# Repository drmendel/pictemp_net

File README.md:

<div align="center">
  
</div>

## Overview

The **`PICTEMP.NET`** is a standalone IoT temperature sensor based on the *PIC18F97J60*, featuring TCP access over Ethernet using the *ENC28J60* ethernet controller. Includes custom firmware built on the Microchip TCP/IP stack and a compact KiCad-designed PC (similar to *PICDEM2.NET*) ideal for IoT, home automation, and industrial monitoring.

The project demonstrates a full-stack IoT solution:

- **Hardware**: A compact, efficient PCB designed in *KiCad*
- **Firmware**: Integrating sensor acquisition and network communication based on *Microchip Solutions v2011-06-02 TCP/IP Demo App*

The project was tested on the *PICDEM2.NET* development board, which ensured the firmware functionality before transitioning to the custom PCB.

## Hardware

### Core Components

- **Microcontroller:** PIC18F97J60  
- **Ethernet Controller:** ENC28J60 (external)  
- **Temperature Sensor:** TC1047x47  
- **Clock Sources:** 25 MHz, 32 kHz crystals  
- **Power Regulation:** LM2940S-5.0, TC1262-3.3  
- **LCD Display:** LCM-S01602DTR_M  
- **Connectivity:** RJ-12, RJ-45, barrel jack, pushbutton, testpoints

*The full list is available in [*pictempnet.csv*](hardware/pictempnet.csv).*

### Design priorities

- Compact footprint for embedded deployment  
- Efficient routing for signals and power  
- Smaller size to reduce cost and complexity    

### PCB Layout

|  |  |  |
|-|-|-|
| *Top view* | *Right view* | *Left view* |

*More images are available in the [images/](hardware/images) folder.*

## Firmware Architecture

The firmware is based on *Microchip Solutions v2011-06-02 TCP/IP Demo App*, modified to implement temperature sensing functionality. Key components include:  

- *`temperature_sensor.h` / `temperature_sensor.c`* – Interfaces directly with the temperature sensor IC, reading real-time measurements and providing functions to access the data.    
- *`GenericTCPIPServer.c`* – Derived from Microchip sources, enhanced for temperature sensor integration and real-time TCP access.

The firmware manages:  

- TCP connection handling and client requests  
- Temperature sensor sampling on TCP request
- Data buffering and formatting
- Efficient, low-latency response for real-time monitoring  

## Usage

### Project Configuration

The firmware is developed using *Microchip MPLAB X IDE*. It is strongly recommended to compile the project with this IDE due to complex configuration requirements.

In the project properties, set the following options:

- **Categories:** `C18-PICDN2_ENC28`  
- **Device:** `PIC18F97J60`  
- **Compiler Toolchain:** *[`C18 v3.47`](https://mplab-c18.software.informer.com/download/)*  

### Steps to Use

1. **Flash** the firmware to the custom *PCB* or the *PICDEM2.NET* development board.  
2. **Connect** the device to your network via Ethernet. The LCD will display the assigned IP address.  
3. **Access** temperature readings by sending the character `'t'` or `'T'` to *TCP port 2000*.

## Licensing

- **Hardware design**: Licensed under the [CERN-OHL-W-2.0](./hardware/LICENSE).  
- **Firmware**: Licensed under the terms of the [MICROCHIP SOFTWARE LICENSE AGREEMENT](./firmware/LICENSE).  

By **`DOWNLOADING`** or **`USING`** any part of this repository (including but not limited to source code, hardware design files, schematics, documentation, and images) through methods such as:
  - cloning the repository (`git clone ...`)  
  - downloading release archives (`.zip` / `.tar.gz`)  
  - forking the repository  
  - downloading individual files via the GitHub web interface  
  - retrieving the repository via GitHub API or GitHub CLI  
  - mirroring the repository

you **`AGREE`** to the applicable license terms, including the [MICROCHIP SOFTWARE LICENSE AGREEMENT](./firmware/LICENSE).

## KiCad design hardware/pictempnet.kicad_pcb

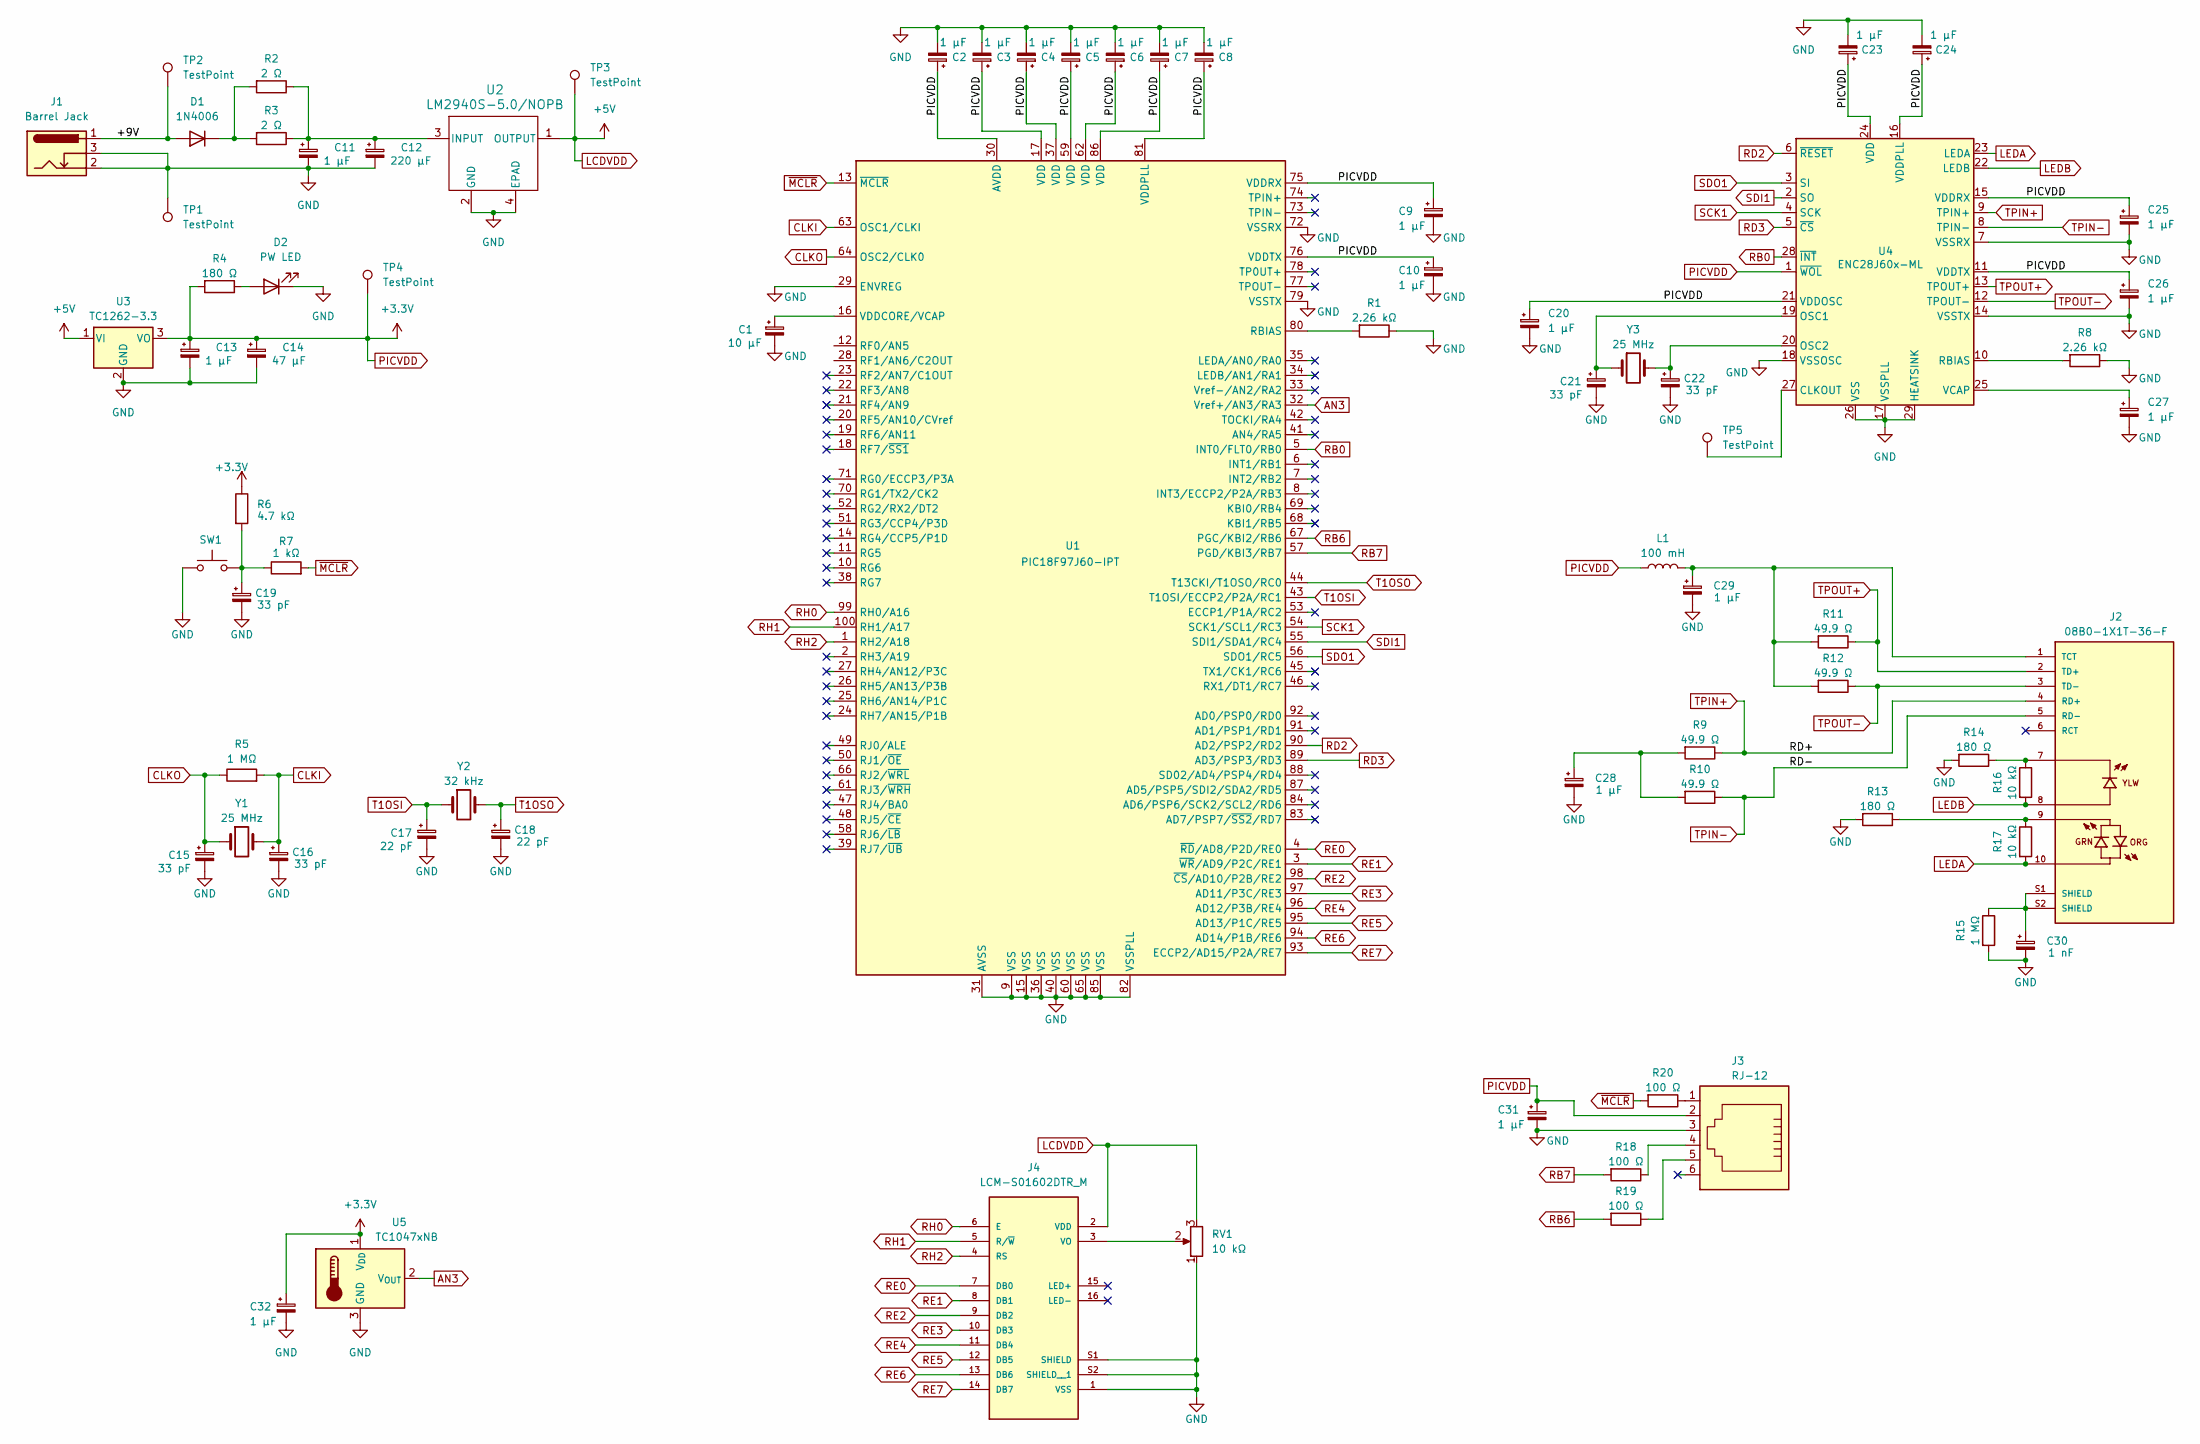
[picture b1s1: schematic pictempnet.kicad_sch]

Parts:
C1: 10 μF; CP_EIA-1608-08_AVX-J_Pad1.25x1.05mm_HandSolder
C2, C3, C4, C5, C6, C7, C8, C9, C10, C11, C13, C20, C23, C24, C25, C26, C27, C28, C29, C31, C32: 1 μF; CP_EIA-1608-08_AVX-J_Pad1.25x1.05mm_HandSolder
C12: 220 μF; CP_EIA-1608-08_AVX-J_Pad1.25x1.05mm_HandSolder
C14: 47 μF; CP_EIA-1608-08_AVX-J_Pad1.25x1.05mm_HandSolder
C15, C16, C19, C21, C22: 33 pF; CP_EIA-1608-08_AVX-J_Pad1.25x1.05mm_HandSolder
C17, C18: 22 pF; CP_EIA-1608-08_AVX-J_Pad1.25x1.05mm_HandSolder
C30: 1 nF; CP_EIA-1608-08_AVX-J_Pad1.25x1.05mm_HandSolder
D1: 1N4006; D_DO-41_SOD81_P10.16mm_Horizontal
D2: PW LED; LED_0805_2012Metric_Pad1.15x1.40mm_HandSolder
J1: Barrel Jack; BarrelJack_CLIFF_FC681465S_SMT_Horizontal
J2: 08B0-1X1T-36-F; BEL_08B0-1X1T-36-F; PARTREV D
J3: RJ-12; RJ12_Amphenol_54601-x06_Horizontal
J4: LCM-S01602DTR_M; LCD_LCM-S01602DTR_M; PARTREV 9/11/02
L1: 100 mH; L_0603_1608Metric_Pad1.05x0.95mm_HandSolder
R1, R8: 2.26 kΩ; R_0603_1608Metric_Pad0.98x0.95mm_HandSolder
R2, R3: 2 Ω; R_1206_3216Metric_Pad1.30x1.75mm_HandSolder
R4, R13, R14: 180 Ω; R_0603_1608Metric_Pad0.98x0.95mm_HandSolder
R5, R15: 1 MΩ; R_0603_1608Metric_Pad0.98x0.95mm_HandSolder
R6: 4.7 kΩ; R_0603_1608Metric_Pad0.98x0.95mm_HandSolder
R7: 1 kΩ; R_0603_1608Metric_Pad0.98x0.95mm_HandSolder
R9, R10, R11, R12: 49.9 Ω; R_0603_1608Metric_Pad0.98x0.95mm_HandSolder
R16, R17: 10 kΩ; R_0603_1608Metric_Pad0.98x0.95mm_HandSolder
R18, R19, R20: 100 Ω; R_0603_1608Metric_Pad0.98x0.95mm_HandSolder
RV1: 10 kΩ; Potentiometer_Bourns_3214W_Vertical
SW1: SW_Push; SW_PUSH_6mm
TP1, TP2, TP3, TP4, TP5: TestPoint; TestPoint_Pad_1.5x1.5mm
U1: PIC18F97J60-IPT; TQFP-100_14x14mm_P0.5mm
U2: LM2940S-5.0/NOPB; LM2940S_5_NOPB_KTT3
U3: TC1262-3.3; TO-263-3_TabPin2
U4: ENC28J60x-ML; QFN-28-1EP_6x6mm_P0.65mm_EP4.8x4.8mm
U5: TC1047xNB; SOT-23
Y1, Y3: 25 MHz; Crystal_SMD_Qantek_QC5CB-2Pin_5x3.2mm
Y2: 32 kHz; Crystal_SMD_TXC_9HT11-2Pin_2.0x1.2mm_HandSoldering

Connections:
/+9V: D1.2 (A), J1.1, TP2.1
AN3: U1.32 (Vref+/AN3/RA3), U5.2 (V_{OUT})
CLKI: C16.1, R5.2, U1.63 (OSC1/CLKI), Y1.2
CLKO: C15.1, R5.1, U1.64 (OSC2/CLK0), Y1.1
GND: C1.2, C2.2, C3.2, C4.2, C5.2, C6.2, C7.2, C8.2, C9.2, C10.2, C11.2, C12.2, C13.2, C14.2, C15.2, C16.2, C17.2, C18.2, C19.2, C20.2, C21.2, C22.2, C23.2, C24.2, C25.2, C26.2, C27.2, C28.2, C29.2, C30.2, C31.2, C32.2, D2.1 (K), J1.2, J1.3, J3.3, J4.1 (VSS), J4.S1 (SHIELD), J4.S2 (SHIELD__1), R1.1, R8.1, R13.2, R14.2, R15.2, RV1.1, SW1.1, TP1.1, U1.9 (VSS), U1.15 (VSS), U1.29 (ENVREG), U1.31 (AVSS), U1.36 (VSS), U1.40 (VSS), U1.60 (VSS), U1.65 (VSS), U1.72 (VSSRX), U1.79 (VSSTX), U1.82 (VSSPLL), U1.85 (VSS), U2.2 (GND), U2.4 (EPAD), U3.2 (GND), U4.7 (VSSRX), U4.14 (VSSTX), U4.17 (VSSPLL), U4.18 (VSSOSC), U4.26 (VSS), U4.29 (HEATSINK), U5.3 (GND)
LCDVDD: J4.2 (VDD), RV1.3, TP3.1, U2.1 (OUTPUT), U3.1 (VI)
LEDA: J2.10, R17.2, U4.23 (LEDA)
LEDB: J2.8, R16.2, U4.22 (LEDB)
unnamed: C19.1, R6.2, R7.1, SW1.2
unnamed: C28.1, R9.2, R10.2
unnamed: C30.1, J2.S1 (SHIELD), J2.S2 (SHIELD), R15.1
unnamed: D1.1 (K), R2.2, R3.2
unnamed: D2.2 (A), R4.1
unnamed: J2.7, R14.1, R16.1
unnamed: J2.9, R13.1, R17.1
unnamed: C29.1, J2.1 (TCT), L1.2, R11.2, R12.2
unnamed: J3.1, R20.1
unnamed: J3.4, R18.1
unnamed: J3.5, R19.1
unnamed: J4.3 (VO), RV1.2
unnamed: R1.2, U1.80 (RBIAS)
unnamed: C1.1, U1.16 (VDDCORE/VCAP)
unnamed: C11.1, C12.1, R2.1, R3.1, U2.3 (INPUT)
unnamed: TP5.1, U4.27 (CLKOUT)
unnamed: C21.1, U4.19 (OSC1), Y3.1
unnamed: C22.1, U4.20 (OSC2), Y3.2
unnamed: R8.2, U4.10 (RBIAS)
unnamed: C27.1, U4.25 (VCAP)
PICVDD: C2.1, C3.1, C4.1, C5.1, C6.1, C7.1, C8.1, C9.1, C10.1, C13.1, C14.1, C20.1, C23.1, C24.1, C25.1, C26.1, C31.1, C32.1, J3.2, L1.1, R4.2, R6.1, TP4.1, U1.17 (VDD), U1.30 (AVDD), U1.37 (VDD), U1.59 (VDD), U1.62 (VDD), U1.75 (VDDRX), U1.76 (VDDTX), U1.81 (VDDPLL), U1.86 (VDD), U3.3 (VO), U4.1 (~WOL), U4.11 (VDDTX), U4.15 (VDDRX), U4.16 (VDDPLL), U4.21 (VDDOSC), U4.24 (VDD), U5.1 (V_{DD})
RB0: U1.5 (INT0/FLT0/RB0), U4.28 (~INT)
RB6: R19.2, U1.67 (PGC/KBI2/RB6)
RB7: R18.2, U1.57 (PGD/KBI3/RB7)
RD2: U1.90 (AD2/PSP2/RD2), U4.6 (~RESET)
RD3: U1.89 (AD3/PSP3/RD3), U4.5 (~CS)
RE0: J4.7 (DB0), U1.4 (~RD/AD8/P2D/RE0)
RE1: J4.8 (DB1), U1.3 (~WR/AD9/P2C/RE1)
RE2: J4.9 (DB2), U1.98 (~CS/AD10/P2B/RE2)
RE3: J4.10 (DB3), U1.97 (AD11/P3C/RE3)
RE4: J4.11 (DB4), U1.96 (AD12/P3B/RE4)
RE5: J4.12 (DB5), U1.95 (AD13/P1C/RE5)
RE6: J4.13 (DB6), U1.94 (AD14/P1B/RE6)
RE7: J4.14 (DB7), U1.93 (ECCP2/AD15/P2A/RE7)
RH0: J4.6 (E), U1.99 (RH0/A16)
RH1: J4.5 (R/~W), U1.100 (RH1/A17)
RH2: J4.4 (RS), U1.1 (RH2/A18)
SCK1: U1.54 (SCK1/SCL1/RC3), U4.4 (SCK)
SDI1: U1.55 (SDI1/SDA1/RC4), U4.2 (SO)
SDO1: U1.56 (SDO1/RC5), U4.3 (SI)
T1OSI: C17.1, U1.43 (T1OSI/ECCP2/P2A/RC1), Y2.1
T1OSO: C18.1, U1.44 (T13CKI/T1OSO/RC0), Y2.2
TPIN+: J2.4 (RD+), R9.1, U4.9 (TPIN+)
TPIN-: J2.5 (RD-), R10.1, U4.8 (TPIN-)
TPOUT+: J2.2 (TD+), R11.1, U4.13 (TPOUT+)
TPOUT-: J2.3 (TD-), R12.1, U4.12 (TPOUT-)
~MCLR: R7.2, R20.2, U1.13 (~MCLR)

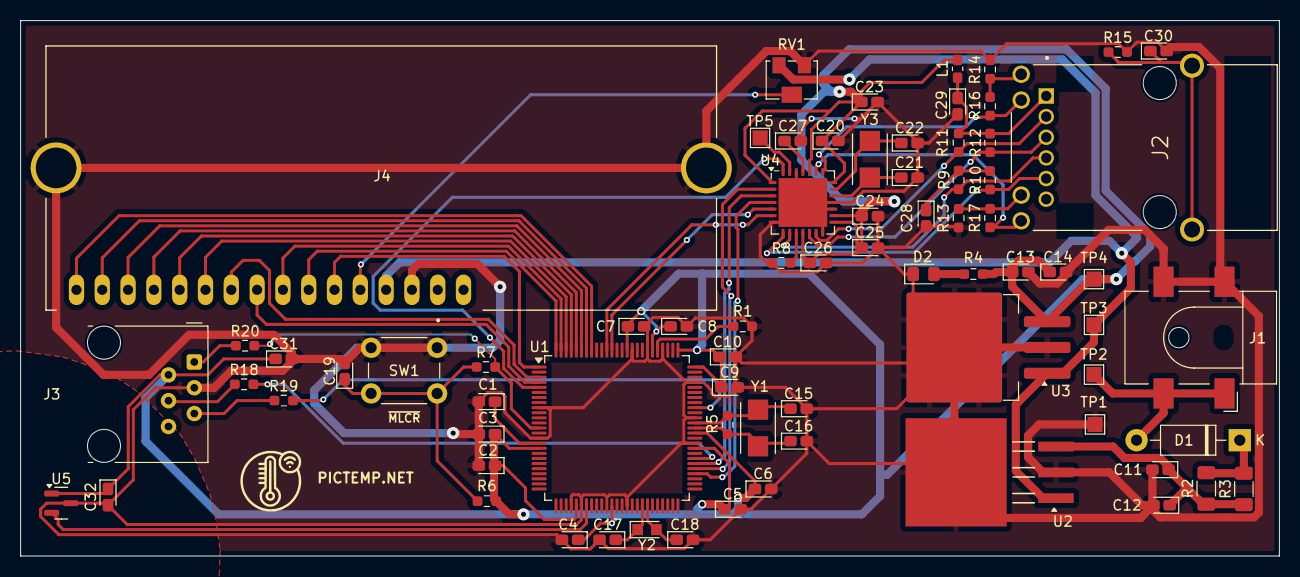
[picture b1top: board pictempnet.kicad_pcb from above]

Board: 2 copper layers, 123.9 x 52.7 mm, 75 parts (0 on the bottom side), 55 nets.

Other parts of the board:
LOGO: LOGO; LOGO_BLACK

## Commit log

2025-09-25 Add Micrichip library from Microchip Solutions v2011-06-02
2025-09-25 Add .gitignore file
2025-09-25 Add TCPIP Demo App from Microchip Solutions v2011-06-02
2025-09-25 Rename 'Demo App' to 'App'
2025-09-25 Add temperature sensor module and update TCP/IP demo projects
    - Added temperature_sensor.c/h for temperature sensor support
    - Updated GenericTCPServer demo app for sensor integration
    - Modified project configuration to support new features
2025-09-25 Add KiCAD files
2025-09-25 Move capacitor closer to IC for better decoupling; reorganize project folders (symbols, footprints, 3D models)
2025-09-25 Update .gitignore file
2025-09-25 Rename MPLAB.X project: PICTEMP.NET
2025-09-25 Add BOM file: pictempnet.csv
2025-09-25 Add PICTEMP.NET logo
2025-09-25 Add license to hardware
2025-09-25 Add license to firmware
2025-09-25 Add README.md
